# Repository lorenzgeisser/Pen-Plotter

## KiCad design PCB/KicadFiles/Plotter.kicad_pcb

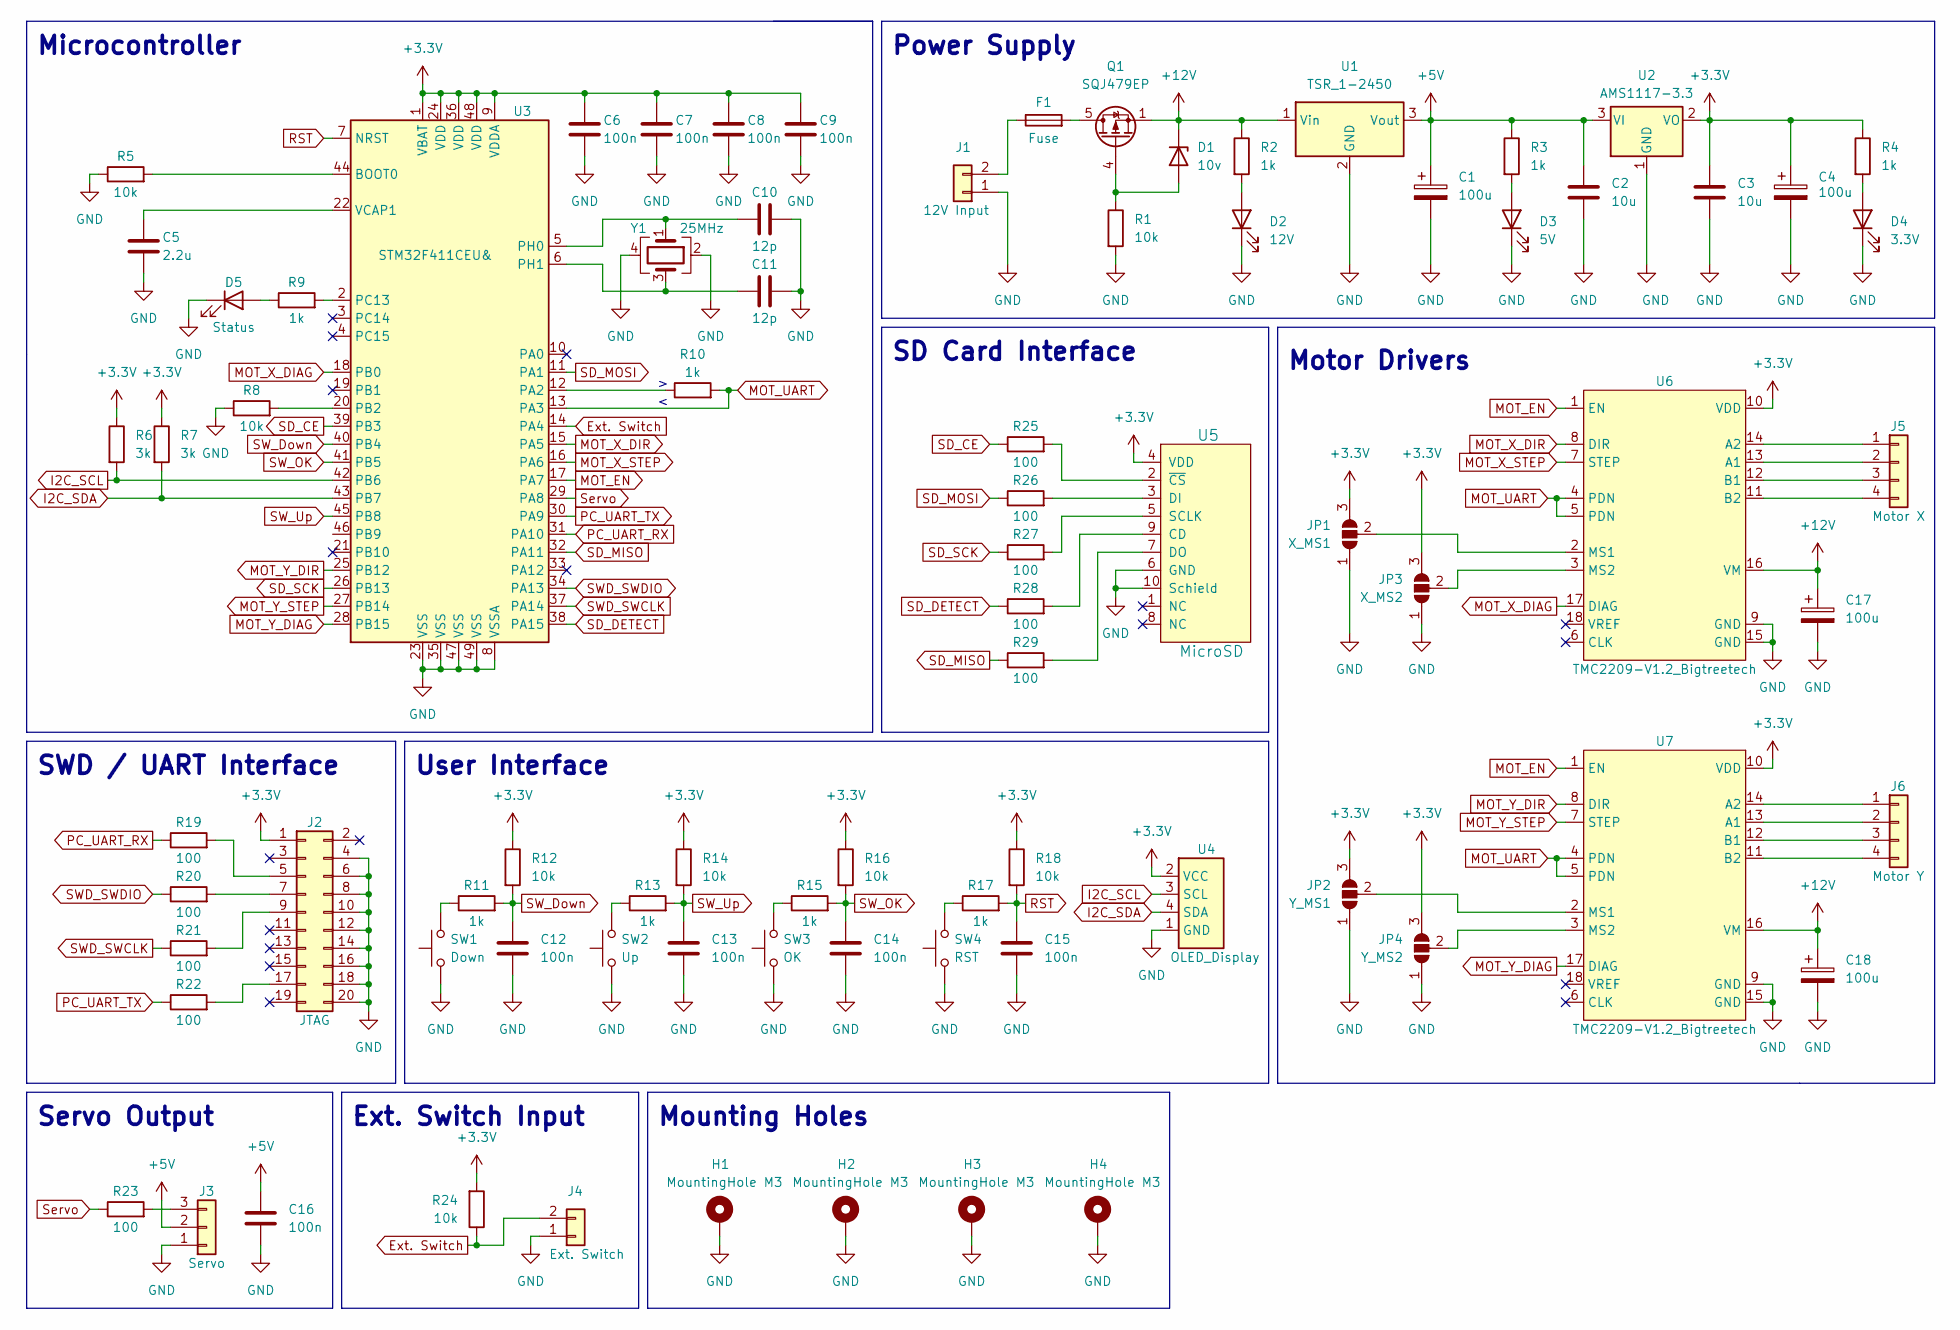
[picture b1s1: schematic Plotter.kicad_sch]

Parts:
C1, C4, C17, C18: 100u; CP_Elec_6.3x7.7
C2, C3: 10u; C_0805_2012Metric
C5: 2.2u; C_0402_1005Metric
C6, C7, C8, C9: 100n; C_0402_1005Metric
C10, C11: 12p; C_0402_1005Metric
C12, C13, C14, C15, C16: 100n; C_0805_2012Metric
D1: 10v; SOT-23
D2: 12V; LED_0805_2012Metric
D3: 5V; LED_0805_2012Metric
D4: 3.3V; LED_0805_2012Metric
D5: Status; LED_0805_2012Metric
F1: Fuse; Fuseholder_Cylinder-5x20mm_Schurter_0031_8201_Horizontal_Op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
H1, H2, H3, H4: MountingHole M3; MountingHole_3.2mm_M3_Pad_Via
J1: 12V Input; JST_XH_B2B-XH-A_1x02_P2.50mm_Vertical
J2: JTAG; IDC-Header_2x10_P2.54mm_Vertical
J3: Servo; JST_XH_B3B-XH-A_1x03_P2.50mm_Vertical
J4: Ext. Switch; JST_XH_B2B-XH-A_1x02_P2.50mm_Vertical
J5: Motor X; JST_XH_B4B-XH-A_1x04_P2.50mm_Vertical
J6: Motor Y; JST_XH_B4B-XH-A_1x04_P2.50mm_Vertical
JP1: X_MS1; SolderJumper-3_P1.3mm_Open_RoundedPad1.0x1.5mm
JP2: Y_MS1; SolderJumper-3_P1.3mm_Open_RoundedPad1.0x1.5mm
JP3: X_MS2; SolderJumper-3_P1.3mm_Open_RoundedPad1.0x1.5mm
JP4: Y_MS2; SolderJumper-3_P1.3mm_Open_RoundedPad1.0x1.5mm
Q1: SQJ479EP; TDSON-8-1
R1, R5, R8, R12, R14, R16, R18, R24: 10k; R_0805_2012Metric
R2, R3, R4, R9, R10, R11, R13, R15, R17: 1k; R_0805_2012Metric
R6, R7: 3k; R_0805_2012Metric
R19, R20, R21, R22, R23, R25, R26, R27, R28, R29: 100; R_0805_2012Metric
SW1: Down; SW_PUSH_6mm_H5mm
SW2: Up; SW_PUSH_6mm_H5mm
SW3: OK; SW_PUSH_6mm_H5mm
SW4: RST; SW_PUSH_6mm_H5mm
U1: TSR_1-2450; Converter_DCDC_TRACO_TSR-1_THT
U2: AMS1117-3.3; SOT-223-3_TabPin2
U3: STM32F411CEU&; QFN-48-1EP_7x7mm_P0.5mm_EP5.6x5.6mm
U4: OLED_Display; Display_128x64_096_I2C
U5: MicroSD; GCT-MEM2055-00-190-01-A
U6, U7: TMC2209-V1.2_Bigtreetech; TMC2209-V1.2 Bigtreetech
Y1: 25MHz; Crystal_SMD_3225-4Pin_3.2x2.5mm

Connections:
+3.3V: C3.1, C4.1, C6.1, C7.1, C8.1, C9.1, J2.1, JP1.3 (B), JP2.3 (B), JP3.3 (B), JP4.3 (B), R4.1, R6.1, R7.1, R12.1, R14.1, R16.1, R18.1, R24.2, U2.2 (VO), U3.1 (VBAT), U3.9 (VDDA), U3.24 (VDD), U3.36 (VDD), U3.48 (VDD), U4.2 (VCC), U5.4 (VDD), U6.10 (VDD), U7.10 (VDD)
+5V: C1.1, C2.1, C16.1, J3.2, R3.1, U1.3 (Vout), U2.3 (VI)
+12V: C17.1, C18.1, D1.3 (K), Q1.1 (S), Q1.2 (S), Q1.3 (S), R2.1, U1.1 (Vin), U6.16 (VM), U7.16 (VM)
Ext. Switch: J4.2, R24.1, U3.14 (PA4)
GND: C1.2, C2.2, C3.2, C4.2, C5.2, C6.2, C7.2, C8.2, C9.2, C10.2, C11.2, C12.2, C13.2, C14.2, C15.2, C16.2, C17.2, C18.2, D2.1 (K), D3.1 (K), D4.1 (K), D5.1 (K), H1.1, H2.1, H3.1, H4.1, J1.1, J2.4, J2.6, J2.8, J2.10, J2.12, J2.14, J2.16, J2.18, J2.20, J3.1, J4.1, JP1.1 (A), JP2.1 (A), JP3.1 (A), JP4.1 (A), R1.2, R5.1, R8.1, SW1.1, SW2.1, SW3.1, SW4.1, U1.2 (GND), U2.1 (GND), U3.8 (VSSA), U3.23 (VSS), U3.35 (VSS), U3.47 (VSS), U3.49 (VSS), U4.1 (GND), U5.6 (GND), U5.10 (Schield), U6.9 (GND), U6.15 (GND), U7.9 (GND), U7.15 (GND), Y1.2, Y1.4
I2C_SCL: R6.2, U3.42 (PB6), U4.3 (SCL)
I2C_SDA: R7.2, U3.43 (PB7), U4.4 (SDA)
MOT_EN: U3.17 (PA7), U6.1 (EN), U7.1 (EN)
MOT_UART: R10.2, U3.13 (PA3), U6.4 (PDN), U6.5 (PDN), U7.4 (PDN), U7.5 (PDN)
MOT_X_DIAG: U3.18 (PB0), U6.17 (DIAG)
MOT_X_DIR: U3.15 (PA5), U6.8 (DIR)
MOT_X_STEP: U3.16 (PA6), U6.7 (STEP)
MOT_Y_DIAG: U3.28 (PB15), U7.17 (DIAG)
MOT_Y_DIR: U3.25 (PB12), U7.8 (DIR)
MOT_Y_STEP: U3.27 (PB14), U7.7 (STEP)
unnamed: C5.1, U3.22 (VCAP1)
unnamed: C10.1, U3.5 (PH0), Y1.1
unnamed: C11.1, U3.6 (PH1), Y1.3
unnamed: D1.1 (A), Q1.4 (G), R1.1
unnamed: D2.2 (A), R2.2
unnamed: D3.2 (A), R3.2
unnamed: D4.2 (A), R4.2
unnamed: D5.2 (A), R9.1
unnamed: F1.1, J1.2
unnamed: F1.2, Q1.5 (D)
unnamed: J2.5, R19.2
unnamed: J2.7, R20.2
unnamed: J2.9, R21.2
unnamed: J2.17, R22.2
unnamed: J3.3, R23.2
unnamed: J5.1, U6.14 (A2)
unnamed: J5.2, U6.13 (A1)
unnamed: J5.3, U6.12 (B1)
unnamed: J5.4, U6.11 (B2)
unnamed: J6.1, U7.14 (A2)
unnamed: J6.2, U7.13 (A1)
unnamed: J6.3, U7.12 (B1)
unnamed: J6.4, U7.11 (B2)
unnamed: JP1.2 (C), U6.2 (MS1)
unnamed: JP2.2 (C), U7.2 (MS1)
unnamed: JP3.2 (C), U6.3 (MS2)
unnamed: JP4.2 (C), U7.3 (MS2)
unnamed: R5.2, U3.44 (BOOT0)
unnamed: R8.2, U3.20 (PB2)
unnamed: R9.2, U3.2 (PC13)
unnamed: R10.1, U3.12 (PA2)
unnamed: R11.1, SW1.2
unnamed: R13.1, SW2.2
unnamed: R15.1, SW3.2
unnamed: R17.1, SW4.2
unnamed: R25.2, U5.2 (~CS)
unnamed: R26.2, U5.3 (DI)
unnamed: R27.2, U5.5 (SCLK)
unnamed: R28.2, U5.9 (CD)
unnamed: R29.2, U5.7 (DO)
PC_UART_RX: R19.1, U3.31 (PA10)
PC_UART_TX: R22.1, U3.30 (PA9)
RST: C15.1, R17.2, R18.2, U3.7 (NRST)
SD_CE: R25.1, U3.39 (PB3)
SD_DETECT: R28.1, U3.38 (PA15)
SD_MISO: R29.1, U3.32 (PA11)
SD_MOSI: R26.1, U3.11 (PA1)
SD_SCK: R27.1, U3.26 (PB13)
SWD_SWCLK: R21.1, U3.37 (PA14)
SWD_SWDIO: R20.1, U3.34 (PA13)
SW_Down: C12.1, R11.2, R12.2, U3.40 (PB4)
SW_OK: C14.1, R15.2, R16.2, U3.41 (PB5)
SW_Up: C13.1, R13.2, R14.2, U3.45 (PB8)
Servo: R23.1, U3.29 (PA8)

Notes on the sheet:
Servo Output
Ext. Switch Input
Motor Drivers
User Interface
Mounting Holes
Microcontroller
SWD / UART Interface
SD Card Interface
Power Supply

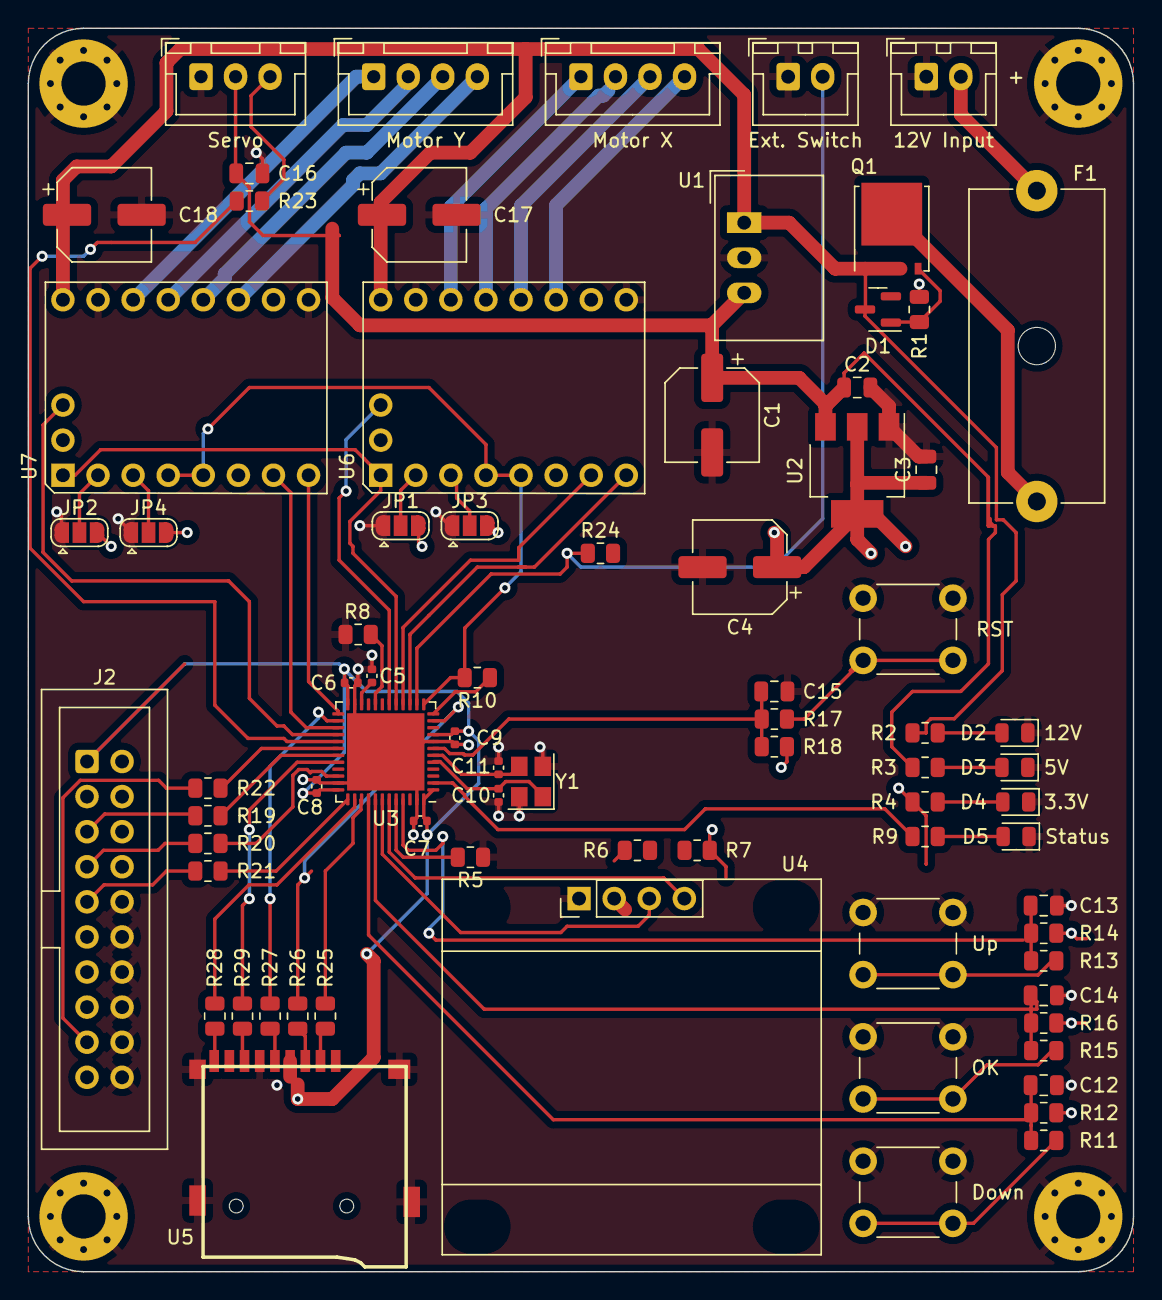
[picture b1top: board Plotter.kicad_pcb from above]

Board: 4 copper layers, 80.0 x 90.0 mm, 80 parts (0 on the bottom side), 69 nets.

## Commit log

2022-05-15 its a start :+1:
2022-05-15 Point can store pen state
2022-05-21 bodge
2022-05-22 more files
2022-05-22 fix spiral
2022-05-27 multitasking baby!!!
2022-05-29 half way done
2022-05-30 const
2022-06-20 ready to mill
2022-06-20 drawings
2022-06-21 fix middle
2022-06-23 KicadProject
2022-06-23 Revert "fix middle"
    This reverts commit 356c8d0eeff1c686e1f9719ac6f8e526ae723223.
2022-06-23 revert
2022-06-23 Kicad
2022-06-23 TMC2209 in Kicad
2022-06-23 gitignore
2022-06-23 use gitignore
2022-06-23 Fix Distanceon Belt Clamp
2022-06-28 testing sensorless homing
2022-06-28 other lib
2022-07-01 stall detect lauft
    https://github.com/teemuatlut/TMCStepper/issues/178
2022-07-02 schematic half way done
2022-07-03 finished schematic
2022-07-07 stm32??
2022-07-11 bald fertig
